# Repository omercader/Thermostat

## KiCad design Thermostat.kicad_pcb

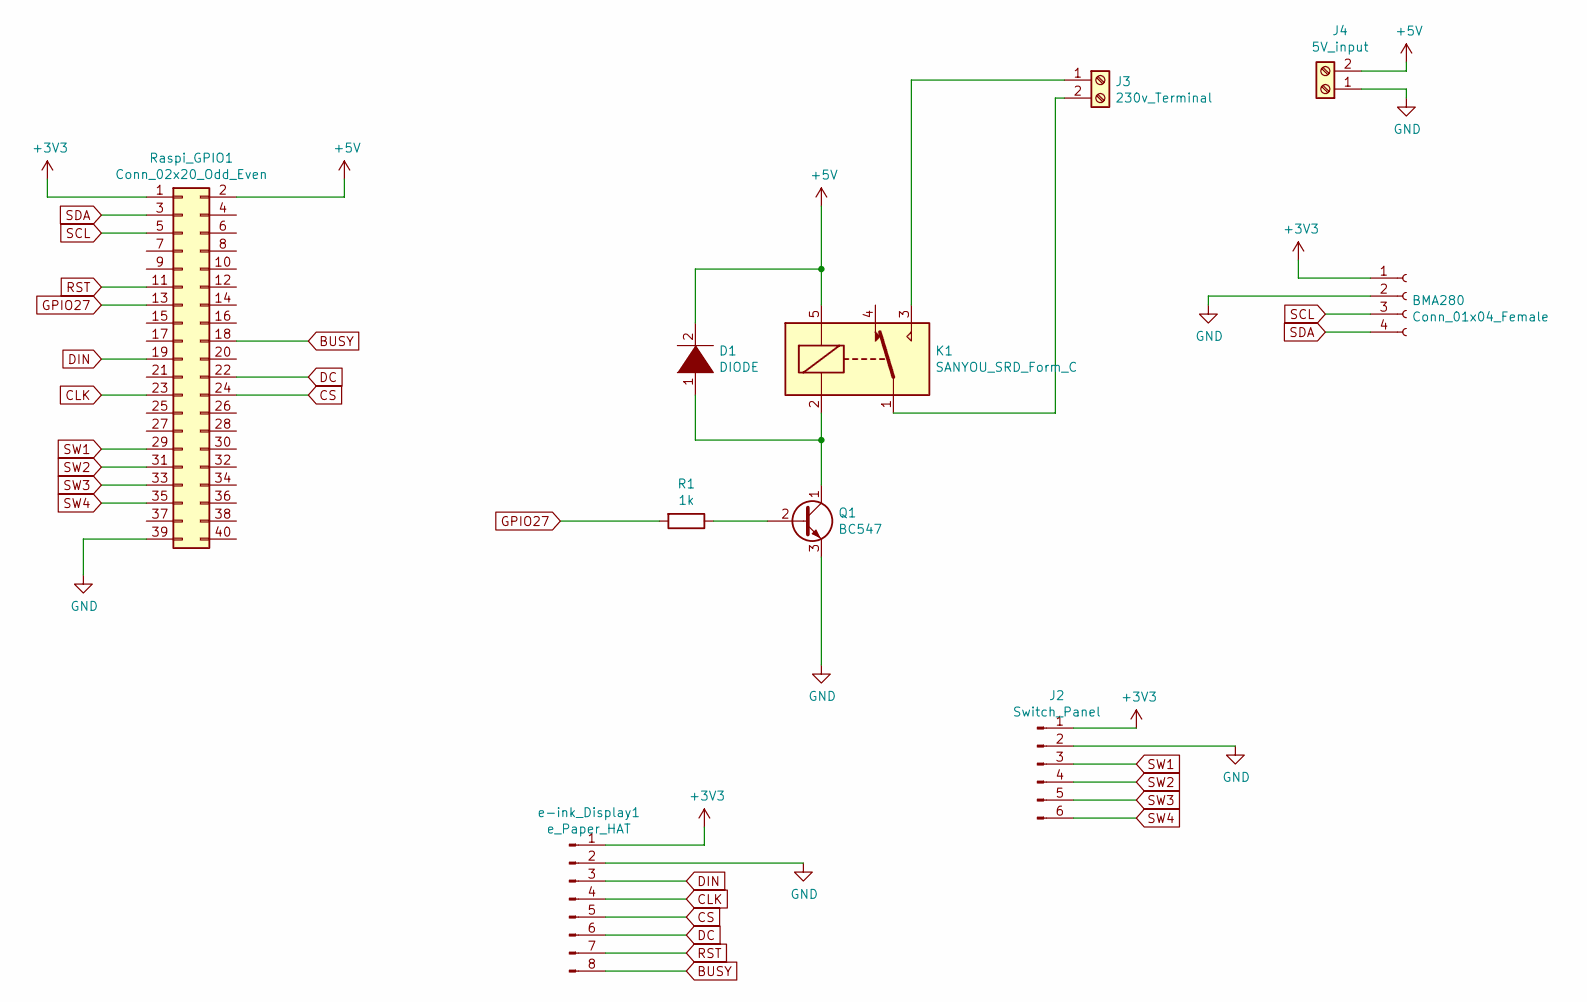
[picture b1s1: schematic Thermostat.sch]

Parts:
BMA280: Conn_01x04_Female; PinHeader_1x04_P1.27mm_Vertical
D1: DIODE; D_A-405_P7.62mm_Horizontal
J2: Switch_Panel; PinHeader_1x06_P1.27mm_Vertical
J3: 230v_Terminal; TerminalBlock_Altech_AK300-2_P5.00mm
J4: 5V_input; TerminalBlock_Altech_AK300-2_P5.00mm
K1: SANYOU_SRD_Form_C; Relay_SPDT_SANYOU_SRD_Series_Form_C
Q1: BC547; TO-92_Inline
R1: 1k; R_Axial_DIN0204_L3.6mm_D1.6mm_P7.62mm_Horizontal
Raspi_GPIO1: Conn_02x20_Odd_Even; PinHeader_2x20_P1.27mm_Vertical
e-ink_Display1: e_Paper_HAT; PinHeader_1x08_P1.27mm_Vertical

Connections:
+3V3: BMA280.1, J2.1, Raspi_GPIO1.1, e-ink_Display1.1
+5V: D1.2 (A), J4.2, K1.5, Raspi_GPIO1.2
BUSY: Raspi_GPIO1.18, e-ink_Display1.8
CLK: Raspi_GPIO1.23, e-ink_Display1.4
CS: Raspi_GPIO1.24, e-ink_Display1.5
DC: Raspi_GPIO1.22, e-ink_Display1.6
DIN: Raspi_GPIO1.19, e-ink_Display1.3
GND: BMA280.2, J2.2, J4.1, Q1.3 (E), Raspi_GPIO1.39, e-ink_Display1.2
GPIO27: R1.2, Raspi_GPIO1.13
unnamed: D1.1 (K), K1.2, Q1.1 (C)
unnamed: J3.1, K1.3
unnamed: J3.2, K1.1
unnamed: Q1.2 (B), R1.1
RST: Raspi_GPIO1.11, e-ink_Display1.7
SCL: BMA280.3, Raspi_GPIO1.5
SDA: BMA280.4, Raspi_GPIO1.3
SW1: J2.3, Raspi_GPIO1.29
SW2: J2.4, Raspi_GPIO1.31
SW3: J2.5, Raspi_GPIO1.33
SW4: J2.6, Raspi_GPIO1.35

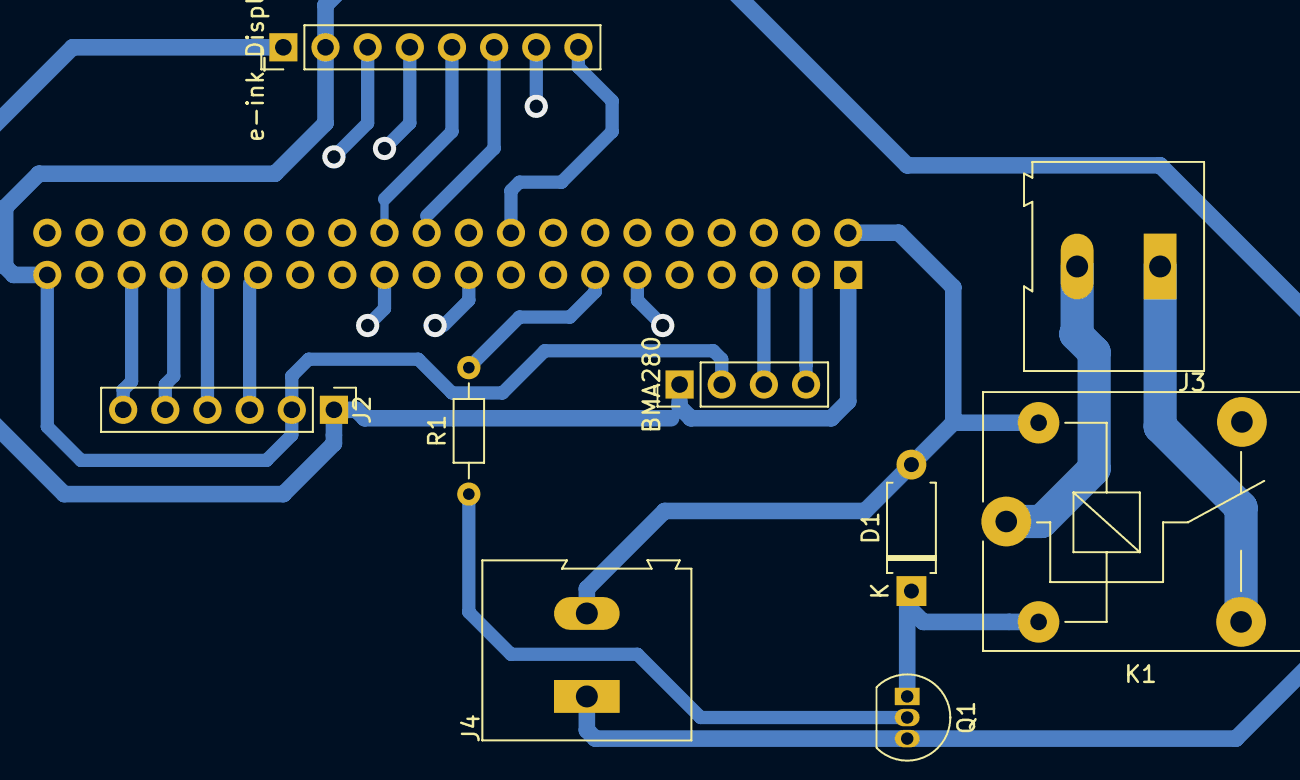
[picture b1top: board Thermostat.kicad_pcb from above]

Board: 2 copper layers, 10 parts (1 on the bottom side), 20 nets.

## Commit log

2020-03-04 new version with gcode parameters midified in order to follow de Cyclone recomendations.
